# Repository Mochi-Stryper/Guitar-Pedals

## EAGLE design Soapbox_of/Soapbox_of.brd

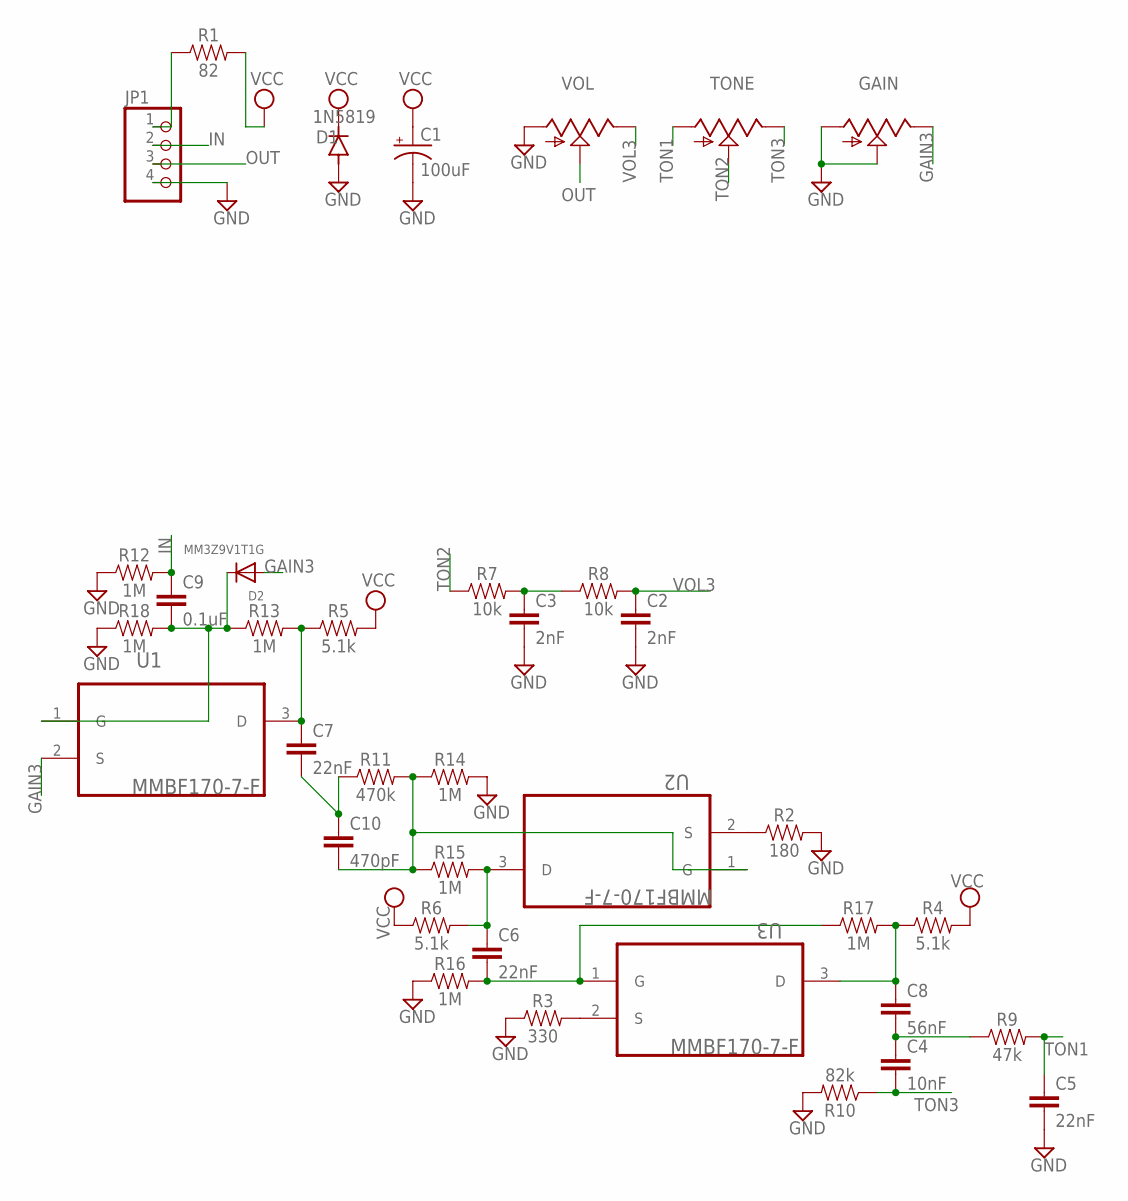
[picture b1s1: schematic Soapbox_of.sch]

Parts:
C1: 100uF; PAN_B_SMD+THRU
C2, C3: 2nF; 0603
C4: 10nF; 0603
C5, C6, C7: 22nF; 0603
C8: 56nF; 0603
C9: 0.1uF; 0603
C10: 470pF; 0603
D1: 1N5819; SOD123
D2: MM3Z9V1T1G; SOD-323F
GAIN: 9MM_SNAP-IN_POT_; 9MM_SNAP-IN_POT
JP1: PINHD-1X4; 1X04
R1: 82; 0603
R2: 180; 0603
R3: 330; 0603
R4, R5, R6: 5.1k; 0603
R7, R8: 10k; 0603
R9: 47k; 0603
R10: 82k; 0603
R11: 470k; 0603
R12, R13, R14, R15, R16, R17, R18: 1M; 0603
TONE: 9MM_SNAP-IN_POT_; 9MM_SNAP-IN_POT
U1, U2, U3: MMBF170-7-F; SOT103P240X110-3N
VOL: 9MM_SNAP-IN_POT_; 9MM_SNAP-IN_POT

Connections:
GAIN3: D2.A, GAIN.3 (E), U1.2 (S)
GND: C1.-, C1.-- (-), C2.2, C3.2, C5.2, D1.A, GAIN.1 (A), GAIN.2 (S), JP1.4, R2.2, R3.1, R10.2, R12.1, R14.2, R16.1, R18.1, VOL.1 (A)
IN: C9.1, JP1.2, R12.2
unnamed: C9.2, D2.C, R13.1, R18.2, U1.1 (G)
unnamed: JP1.1, R1.1
unnamed: R2.1, U2.2 (S)
unnamed: C7.1, R5.1, R13.2, U1.3 (D)
unnamed: C7.2, C10.1, R11.1
unnamed: C10.2, R11.2, R14.1, R15.1, U2.1 (G)
unnamed: C6.1, R6.2, R15.2, U2.3 (D)
unnamed: C6.2, R16.2, R17.1, U3.1 (G)
unnamed: C8.1, R4.1, R17.2, U3.3 (D)
unnamed: C4.1, C8.2, R9.1
unnamed: R3.2, U3.2 (S)
unnamed: C3.1, R7.2, R8.1
OUT: JP1.3, VOL.2 (S)
TON1: C5.1, R9.2, TONE.1 (A)
TON2: R7.1, TONE.2 (S)
TON3: C4.2, R10.1, TONE.3 (E)
VCC: C1.+, C1.++ (+), D1.C, R1.2, R4.2, R5.2, R6.1
VOL3: C2.1, R8.2, VOL.3 (E)

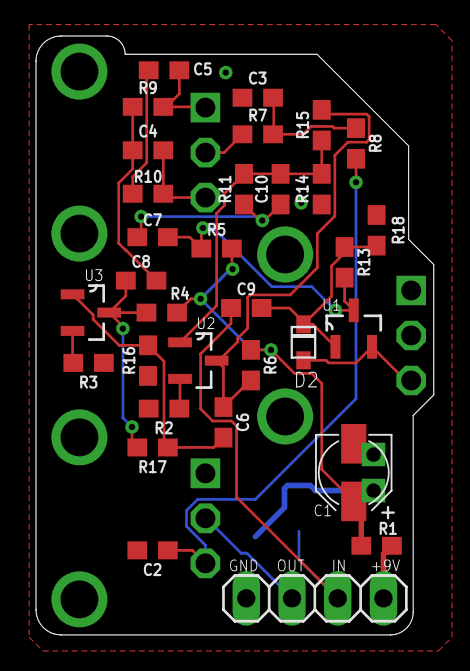
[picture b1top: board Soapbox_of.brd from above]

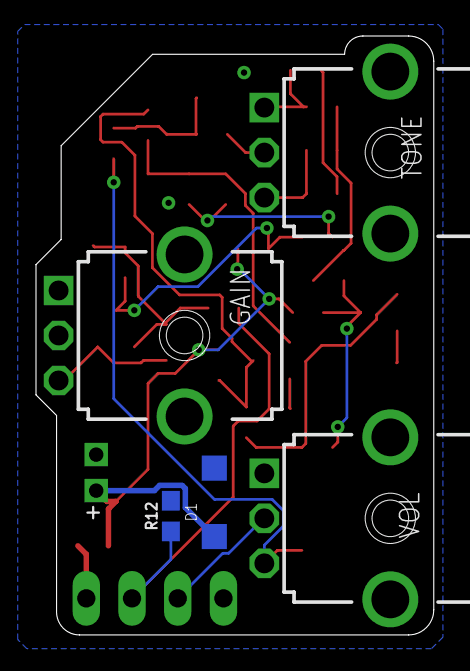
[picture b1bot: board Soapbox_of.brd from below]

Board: 2 copper layers, 22.1 x 33.3 mm, 37 parts (5 on the bottom side), 21 nets.

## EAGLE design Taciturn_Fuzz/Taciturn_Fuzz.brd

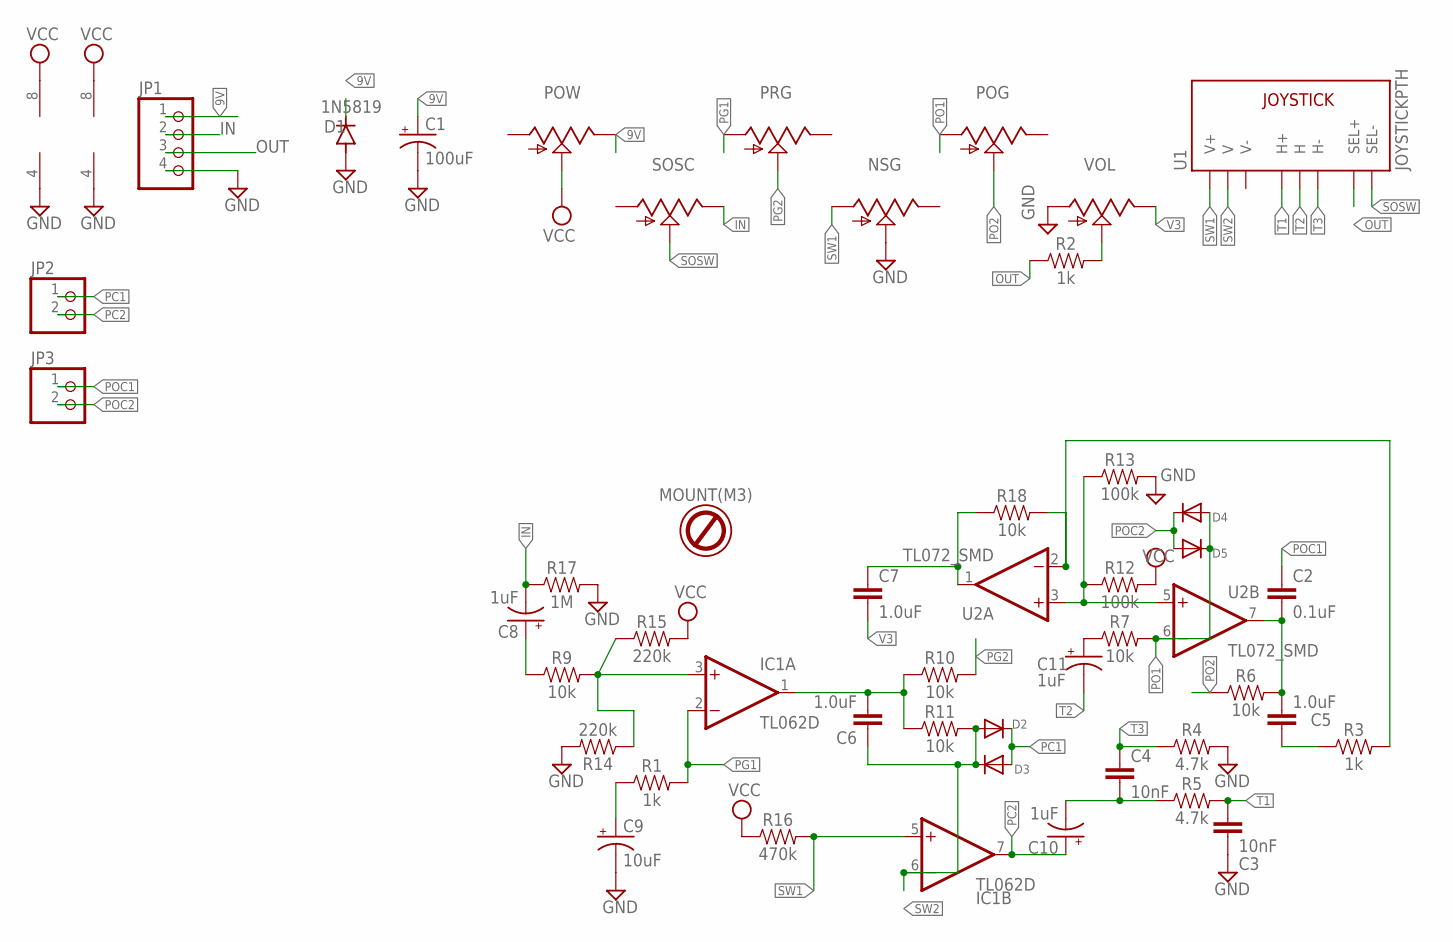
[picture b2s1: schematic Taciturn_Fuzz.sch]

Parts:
C1: 100uF; PAN_B_SMD+THRU
C2: 0.1uF; 0603
C3, C4: 10nF; 0603
C5, C6, C7: 1.0uF; 0603
C8, C10, C11: 1uF; PAN_B_SMD+THRU
C9: 10uF; PAN_B_SMD+THRU
D1: 1N5819; SOD123
D2, D3, D4, D5: DIODESMA; SMADIODE
IC1: TL062D; SO08
JP1: PINHD-1X4; 1X04
JP2, JP3: PINHD-1X2; 1X02
NSG: 9MM_SNAP-IN_POT_; 9MM_SNAP-IN_POT
O1: MOUNT(M3); HOLE-3.5MM
POG: 9MM_SNAP-IN_POT_; 9MM_SNAP-IN_POT
POW: 9MM_SNAP-IN_POT_; 9MM_SNAP-IN_POT
PRG: 9MM_SNAP-IN_POT_; 9MM_SNAP-IN_POT
R1, R2, R3: 1k; 0603
R4, R5: 4.7k; 0603
R6, R7, R9, R10, R11, R18: 10k; 0603
R12, R13: 100k; 0603
R14, R15: 220k; 0603
R16: 470k; 0603
R17: 1M; 0603
SOSC: 9MM_SNAP-IN_POT_; 9MM_SNAP-IN_POT
U1: JOYSTICKPTH; JOYSTICK
U2: TL072_SMD; SO08
VOL: 9MM_SNAP-IN_POT_; 9MM_SNAP-IN_POT

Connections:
9V: C1.+, C1.++ (+), D1.C, JP1.1, POW.3 (E)
GND: C1.-, C1.-- (-), C3.2, C9.-, C9.-- (-), D1.A, IC1.4 (V-), JP1.4, NSG.2 (S), R4.2, R13.2, R14.2, R17.2, U2.4 (V-), VOL.1 (A)
IN: C8.-, C8.-- (-), JP1.2, R17.1, SOSC.3 (E)
unnamed: R3.2, R18.2, U2.2 (-IN)
unnamed: C8.+, C8.++ (+), R9.1
unnamed: IC1.3 (+IN), R9.2, R14.1, R15.1
unnamed: C9.+, C9.++ (+), R1.1
unnamed: C6.2, IC1.1 (OUT), R10.1, R11.1
unnamed: C4.2, C10.-, C10.-- (-), R5.1
unnamed: C11.+, C11.++ (+), R7.1
unnamed: C2.2, C5.1, R6.2, U2.7 (OUT)
unnamed: C5.2, R3.1
unnamed: R12.1, R13.1, U2.3 (+IN), U2.5 (+IN)
unnamed: C7.1, R18.1, U2.1 (OUT)
OUT: JP1.3, R2.1, U1.B1A (SEL+)
PC1: D2.C, D3.A, JP2.1
PC2: C10.+, C10.++ (+), IC1.7 (OUT), JP2.2
PG1: IC1.2 (-IN), PRG.1 (A), R1.2
PG2: PRG.2 (S), R10.2
PO1: D4.A, D5.C, POG.1 (A), R7.2, U2.6 (-IN)
PO2: POG.2 (S), R6.1
POC1: C2.1, JP3.1
POC2: D4.C, D5.A, JP3.2
SOSW: SOSC.2 (S), U1.B2A (SEL-)
SW1: IC1.5 (+IN), NSG.1 (A), R16.2, U1.V1 (V+)
SW2: C6.1, D2.A, D3.C, IC1.6 (-IN), R11.2, U1.V2 (V)
T1: C3.1, R5.2, U1.H1 (H+)
T2: C11.-, C11.-- (-), U1.H2 (H)
T3: C4.1, R4.1, U1.H3 (H-)
V2: R2.2, VOL.2 (S)
V3: C7.2, VOL.3 (E)
VCC: IC1.8 (V+), POW.2 (S), R12.2, R15.2, R16.1, U2.8 (V+)

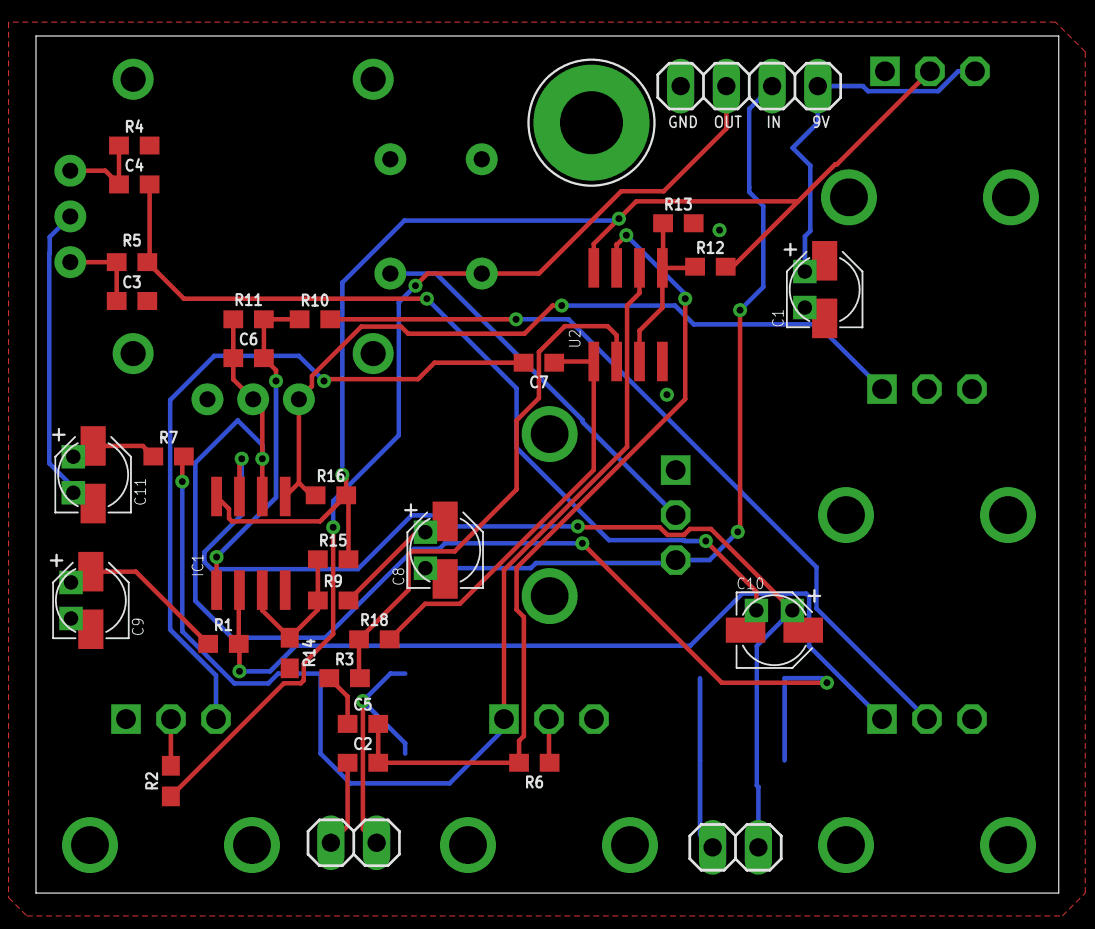
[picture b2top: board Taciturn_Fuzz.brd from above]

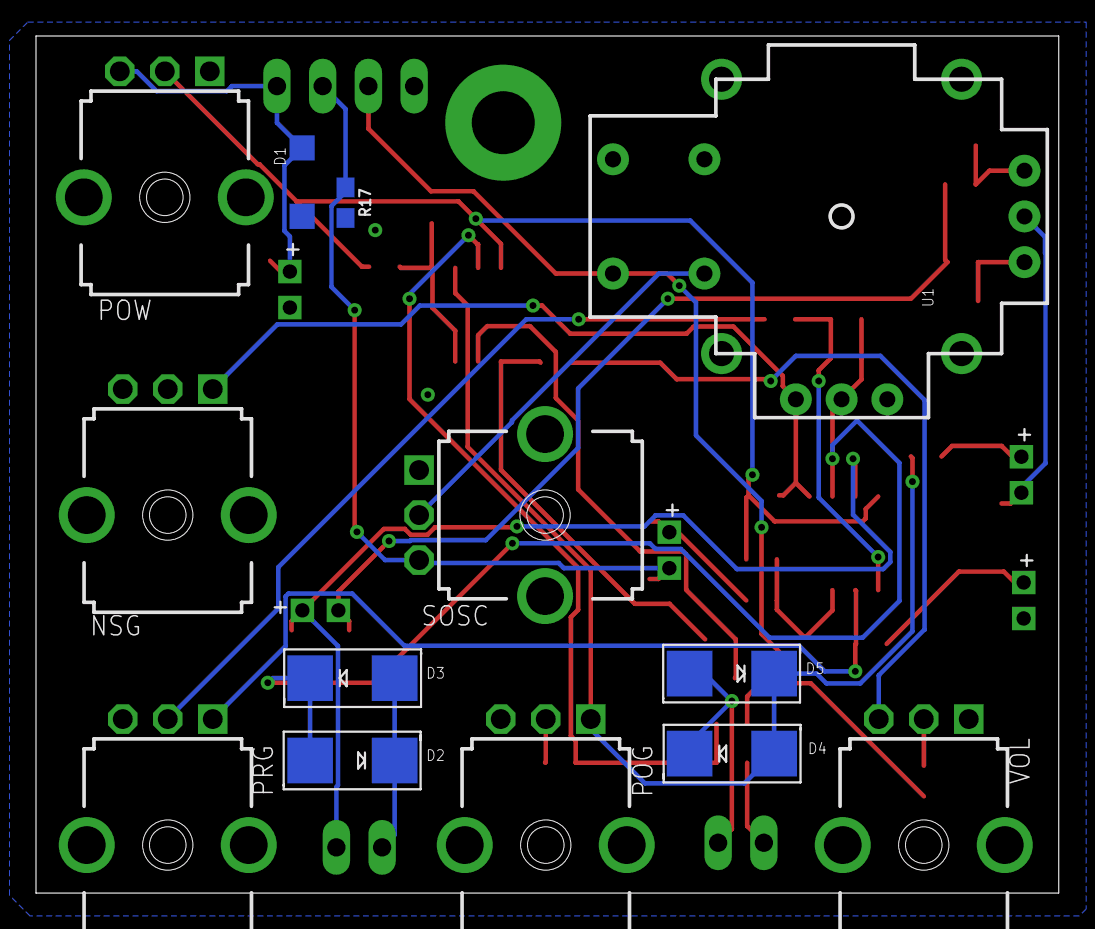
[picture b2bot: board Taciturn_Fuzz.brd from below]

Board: 2 copper layers, 56.8 x 47.6 mm, 46 parts (13 on the bottom side), 32 nets.

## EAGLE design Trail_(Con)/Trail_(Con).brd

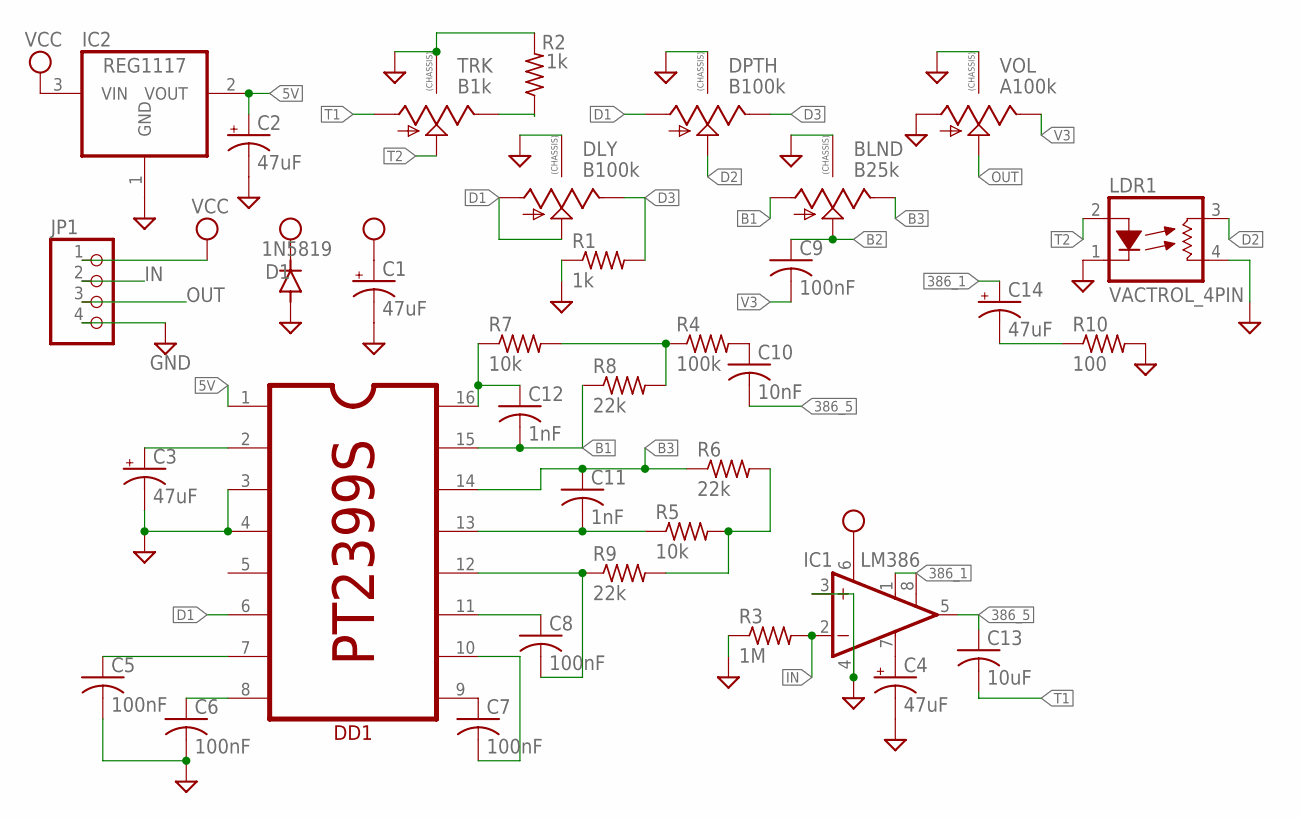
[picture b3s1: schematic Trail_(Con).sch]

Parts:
BLND: B25k; 9MM_SNAP-IN_POT
C1, C2, C3, C4, C14: 47uF; PAN_B_SMD+THRU
C5, C6, C7, C8, C9: 100nF; C0402
C10: 10nF; C0402
C11, C12: 1nF; C0402
C13: 10uF; C0805
D1: 1N5819; SOD123
DD1: PT2399S; SO-16
DLY: B100k; 9MM_SNAP-IN_POT
DPTH: B100k; 9MM_SNAP-IN_POT
IC1: LM386; SO08
IC2: REG1117; SOT223
JP1: PINHD-1X4; 1X04
LDR1: VACTROL_4PIN; VACTROL_4PIN_VTL5C
R1, R2: 1k; R0402
R3: 1M; R0402
R4: 100k; R0402
R5, R7: 10k; R0402
R6, R8, R9: 22k; R0402
R10: 100; R0402
TRK: B1k; 9MM_SNAP-IN_POT
VOL: A100k; 9MM_SNAP-IN_POT

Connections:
5V: C2.+, C2.++ (+), DD1.1, IC2.2 (VOUT)
386_1: C14.+, C14.++ (+), IC1.1 (GAIN), IC1.8 (GAIN)
386_5: C10.2, C13.1, IC1.5 (OUT)
B1: BLND.1 (A), C12.2, DD1.15, R8.1
B2: BLND.2 (S), C9.1
B3: BLND.3 (E), C11.1, DD1.14, R6.1
D1: DD1.6, DLY.1 (A), DLY.2 (S), DPTH.1 (A)
D2: DPTH.2 (S), LDR1.3 (RES1)
D3: DLY.3 (E), DPTH.3 (E), R1.2
GND: BLND.CHASSIS1, BLND.CHASSIS2, C1.-, C1.-- (-), C2.-, C2.-- (-), C3.-, C3.-- (-), C4.-, C4.-- (-), C5.2, C6.2, D1.A, DD1.3, DD1.4, DLY.CHASSIS1, DLY.CHASSIS2, DPTH.CHASSIS1, DPTH.CHASSIS2, IC1.3 (+IN), IC1.4 (GND), IC2.1 (GND), JP1.4, LDR1.1 (LED-), LDR1.4 (RES2), R1.1, R2.2, R3.1, R10.2, TRK.CHASSIS1, TRK.CHASSIS2, VOL.1 (A), VOL.CHASSIS1, VOL.CHASSIS2
IN: IC1.2 (-IN), JP1.2, R3.2
unnamed: C3.+, C3.++ (+), DD1.2
unnamed: C5.1, DD1.7
unnamed: C6.1, DD1.8
unnamed: C7.1, DD1.9
unnamed: C7.2, DD1.10
unnamed: C8.1, DD1.11
unnamed: C8.2, DD1.12, R9.1
unnamed: C11.2, DD1.13, R5.1
unnamed: R5.2, R6.2, R9.2
unnamed: C12.1, DD1.16, R7.1
unnamed: R4.1, R7.2, R8.2
unnamed: C10.1, R4.2
unnamed: R2.1, TRK.3 (E)
unnamed: C4.+, C4.++ (+), IC1.7 (BYPASS)
unnamed: C14.-, C14.-- (-), R10.1
OUT: JP1.3, VOL.2 (S)
T1: C13.2, TRK.1 (A)
T2: LDR1.2 (LED+), TRK.2 (S)
V3: C9.2, VOL.3 (E)
VCC: C1.+, C1.++ (+), D1.C, IC1.6 (VS), IC2.3 (VIN), JP1.1

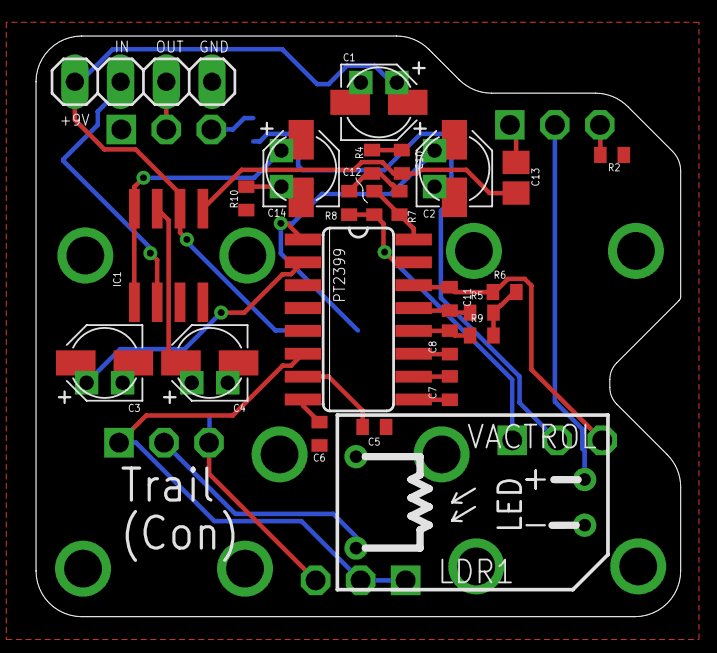
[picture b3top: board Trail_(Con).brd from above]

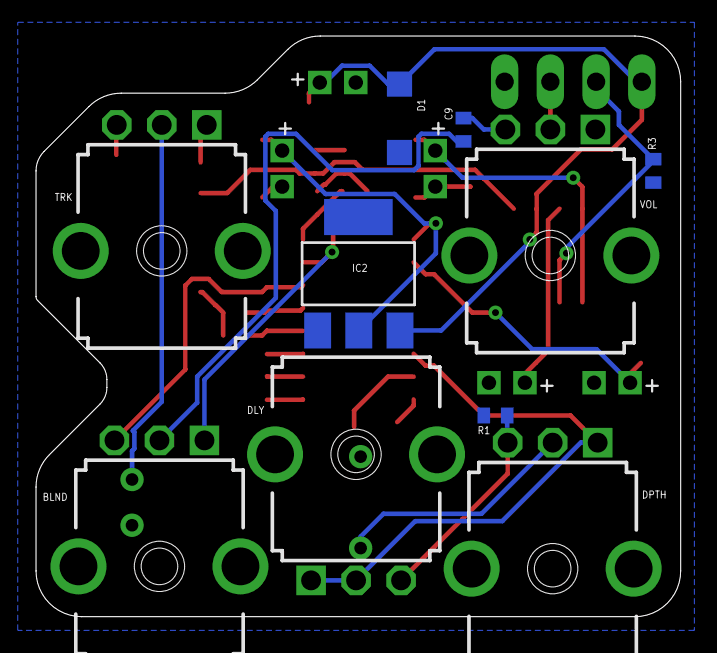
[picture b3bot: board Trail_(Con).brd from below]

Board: 2 copper layers, 35.8 x 32.3 mm, 35 parts (10 on the bottom side), 31 nets.

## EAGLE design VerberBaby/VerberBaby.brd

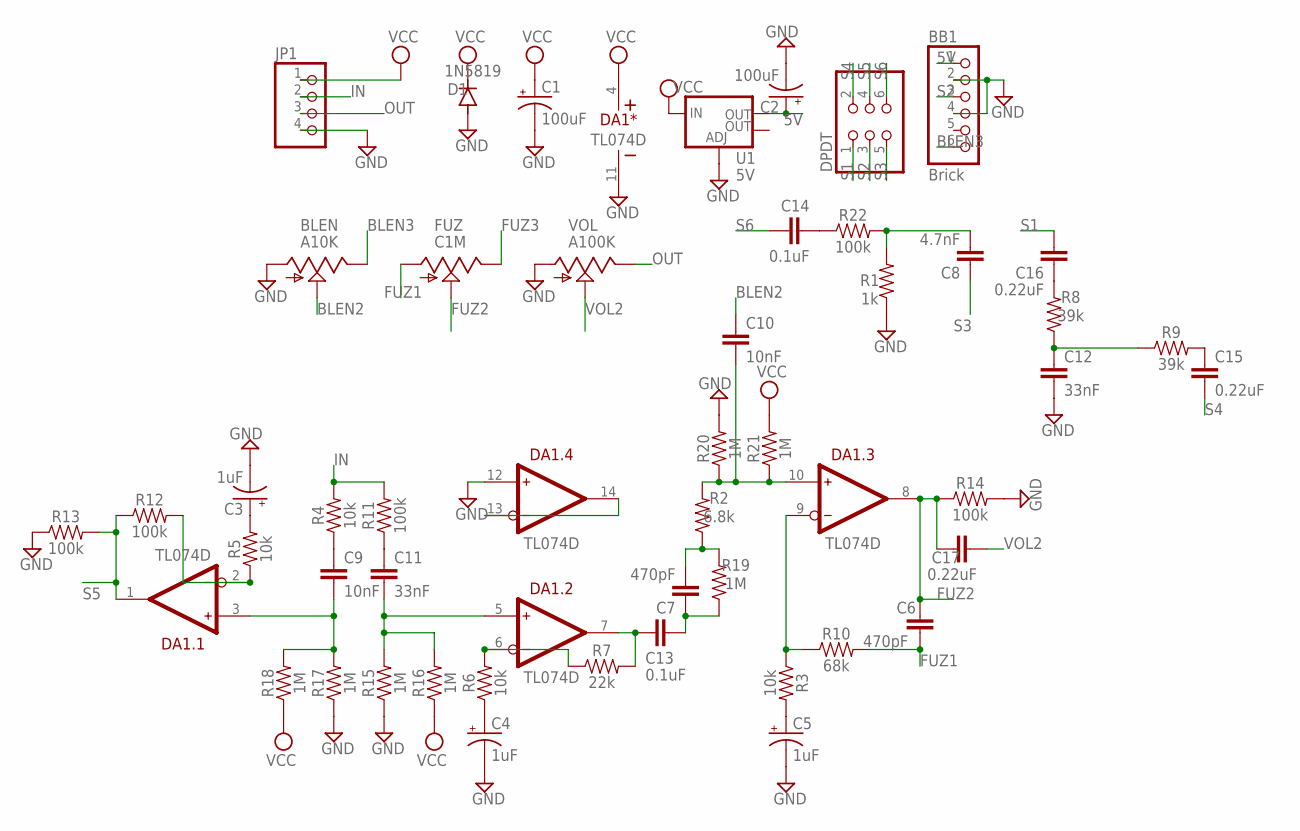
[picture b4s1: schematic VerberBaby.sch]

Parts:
BB1: Brick; 1X06
BLEN: A10K; 9MM_SNAP-IN_POT
C1, C2: 100uF; PAN_B_SMD+THRU
C3, C4, C5: 1uF; PAN_B_SMD+THRU
C6, C7: 470pF; 0603
C8: 4.7nF; 0603
C9, C10: 10nF; 0603
C11, C12: 33nF; 0603
C13, C14: 0.1uF; 0603
C15, C16, C17: 0.22uF; 0603
D1: 1N5819; SOD123
DA1: TL074D; SO-14
DPDT: PINHD-2X3; 2X03
FUZ: C1M; 9MM_SNAP-IN_POT
JP1: PINHD-1X4; 1X04
R1: 1k; 0603
R2: 6.8k; 0603
R3, R4, R5, R6: 10k; 0603
R7: 22k; 0603
R8, R9: 39k; 0603
R10: 68k; 0603
R11, R12, R13, R14, R22: 100k; 0603
R15, R16, R17, R18, R19, R20, R21: 1M; 0603
U1: 5V; SOT223
VOL: A100K; 9MM_SNAP-IN_POT

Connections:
5V: BB1.1, C2.+, C2.++ (+), U1.2 (OUT)
BLEN2: BLEN.2 (S), C10.1
BLEN3: BB1.6, BLEN.3 (E)
FUZ1: C6.2, FUZ.1 (A), R10.2
FUZ2: C6.1, C17.1, DA1.8 (OUT), FUZ.2 (S), R14.1
FUZ3: FUZ.3 (E)
GND: BB1.2, BB1.4, BLEN.1 (A), C1.-, C1.-- (-), C2.-, C2.-- (-), C3.-, C3.-- (-), C4.-, C4.-- (-), C5.-, C5.-- (-), C12.2, D1.A, DA1.11 (V-), DA1.12 (IN+), JP1.4, R1.1, R13.1, R14.2, R15.1, R17.1, R20.2, U1.1 (ADJ), VOL.1 (A)
IN: JP1.2, R4.2, R11.2
N1: DA1.9 (IN-), R3.1, R10.1
unnamed: C11.1, R11.1
unnamed: C9.1, R4.1
unnamed: C11.2, DA1.5 (IN+), R15.2, R16.2
unnamed: C9.2, DA1.3 (IN+), R17.2, R18.2
unnamed: DA1.2 (IN-), R5.1, R12.2
unnamed: C3.+, C3.++ (+), R5.2
unnamed: DA1.6 (IN-), R6.2, R7.1
unnamed: C4.+, C4.++ (+), R6.1
unnamed: C13.2, DA1.7 (OUT), R7.2
unnamed: C7.1, C13.1, R19.1
unnamed: C7.2, R2.1, R19.2
unnamed: C10.2, DA1.10 (IN+), R2.2, R20.1, R21.1
unnamed: DA1.13 (IN-), DA1.14 (OUT)
unnamed: C5.+, C5.++ (+), R3.2
unnamed: C14.2, R22.1
unnamed: C8.2, R1.2, R22.2
unnamed: C16.1, R8.2
unnamed: C12.1, R8.1, R9.1
unnamed: C15.1, R9.2
OUT: JP1.3, VOL.3 (E)
S1: C16.2, DPDT.1
S2: BB1.3, DPDT.3
S3: C8.1, DPDT.5
S4: C15.2, DPDT.2
S5: DA1.1 (OUT), DPDT.4, R12.1, R13.2
S6: C14.1, DPDT.6
VCC: C1.+, C1.++ (+), D1.C, DA1.4 (V+), JP1.1, R16.1, R18.1, R21.2, U1.3 (IN)
VOL2: C17.2, VOL.2 (S)

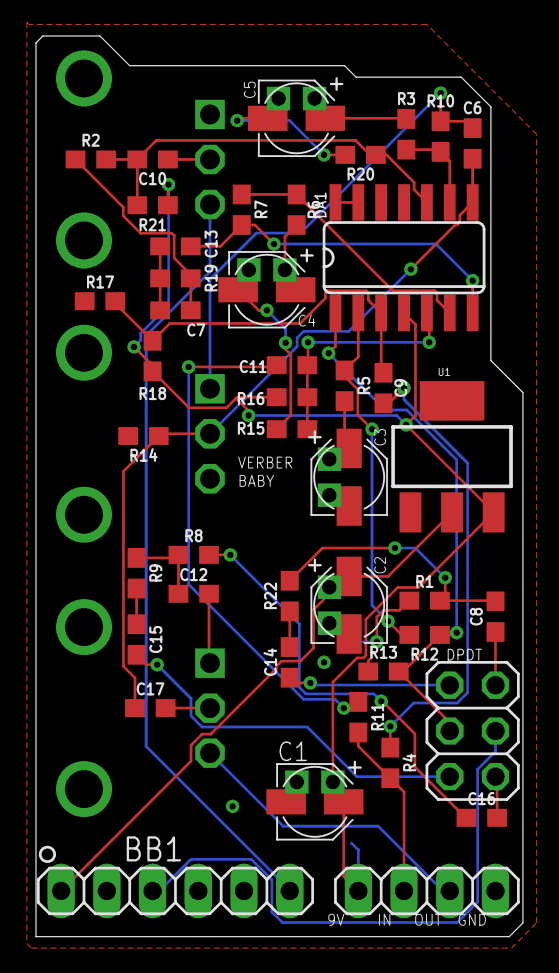
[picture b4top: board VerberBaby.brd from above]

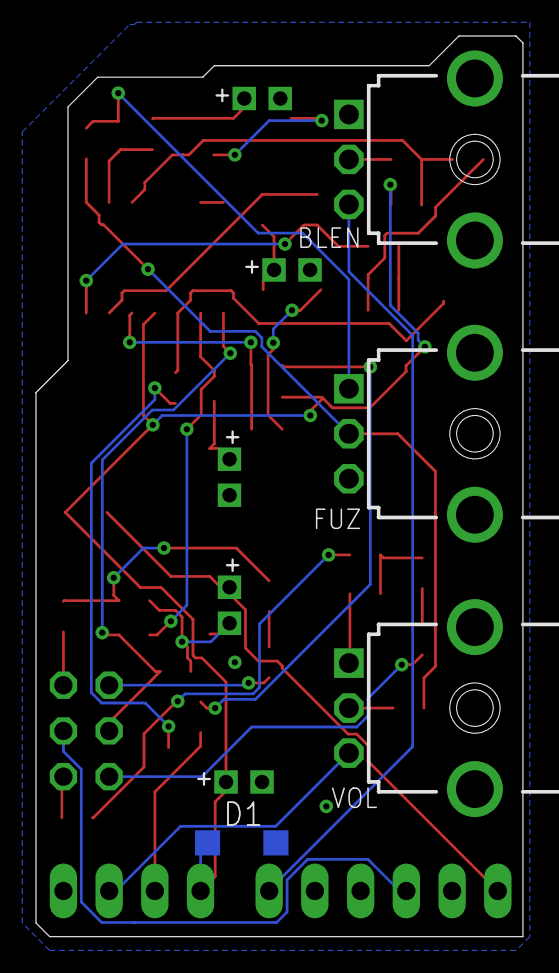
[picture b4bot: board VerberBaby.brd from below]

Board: 2 copper layers, 27.1 x 50.0 mm, 48 parts (4 on the bottom side), 36 nets.

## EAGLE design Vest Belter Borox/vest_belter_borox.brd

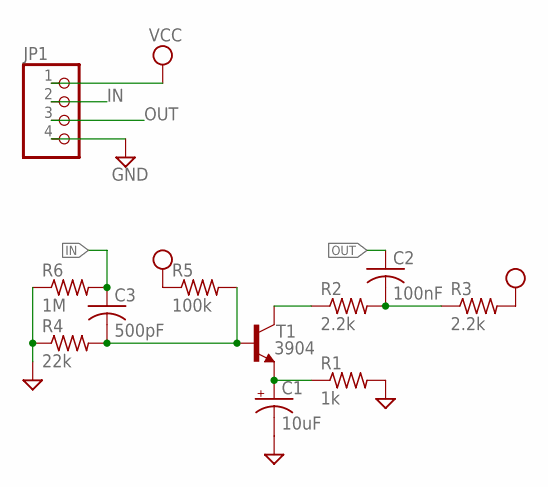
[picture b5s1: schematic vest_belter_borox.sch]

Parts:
C1: 10uF; CAPMP3216X180N
C2: 100nF; C0603
C3: 500pF; C0603
JP1: PINHD-1X4; 1X04
R1: 1k; R0603
R2, R3: 2.2k; R0603
R4: 22k; R0603
R5: 100k; R0603
R6: 1M; R0603
T1: 3904; SOT23-BEC

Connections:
GND: C1.2 (-), JP1.4, R1.2, R4.1, R6.1
IN: C3.1, JP1.2, R6.2
unnamed: C3.2, R4.2, R5.2, T1.B
unnamed: C1.1 (+), R1.1, T1.E
unnamed: C2.2, R2.2, R3.1
unnamed: R2.1, T1.C
OUT: C2.1, JP1.3
VCC: JP1.1, R3.2, R5.1

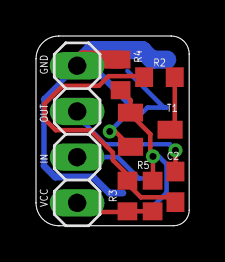
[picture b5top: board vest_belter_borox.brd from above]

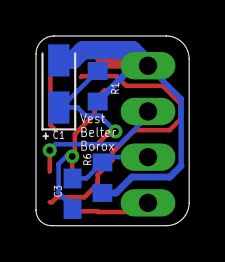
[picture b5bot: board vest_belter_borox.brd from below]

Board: 2 copper layers, 8.5 x 10.5 mm, 11 parts (4 on the bottom side), 8 nets.

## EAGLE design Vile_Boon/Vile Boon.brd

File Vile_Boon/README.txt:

Nocentelli on FSB
Magnalous LuneVibe
Tremolo/Vibrato

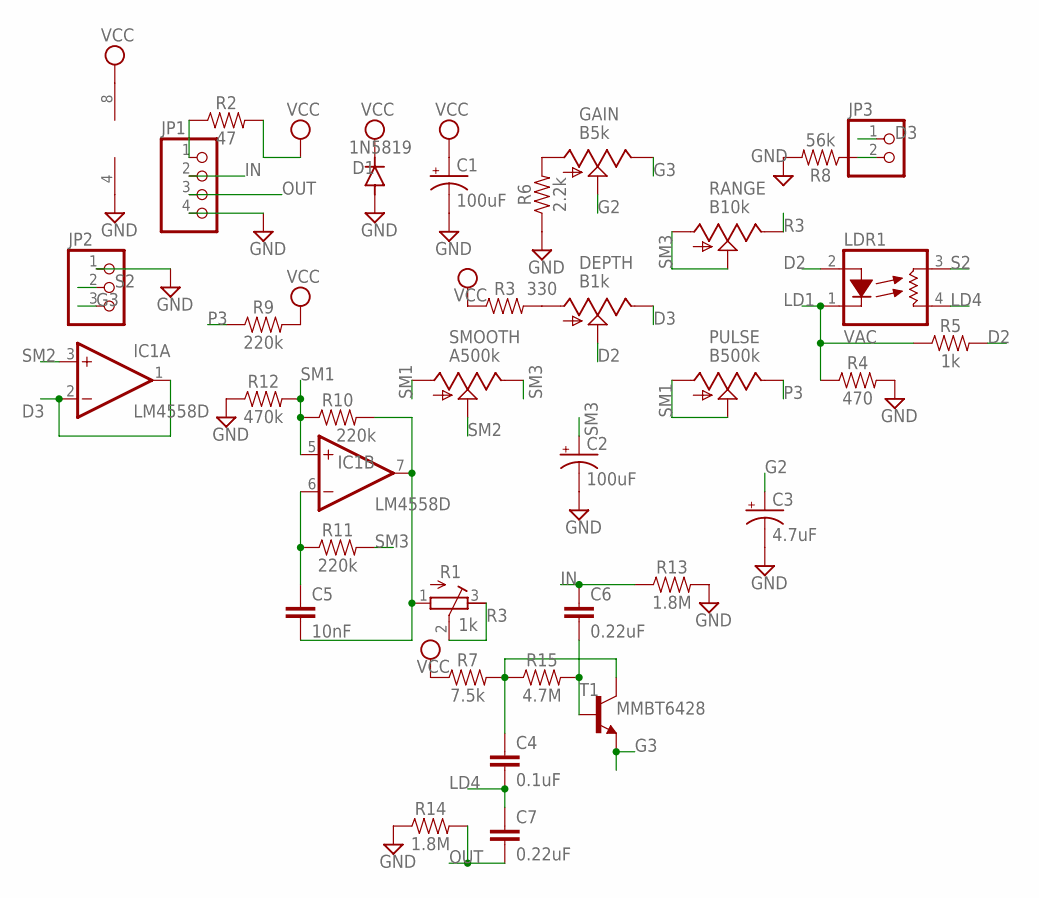
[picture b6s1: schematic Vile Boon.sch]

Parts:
C1, C2: 100uF; PAN_B_SMD+THRU
C3: 4.7uF; PAN_B_SMD+THRU
C4: 0.1uF; 0603
C5: 10nF; 0603
C6, C7: 0.22uF; 0603
D1: 1N5819; SOD123
DEPTH: B1k; 9MM_SNAP-IN_POT
GAIN: B5k; 9MM_SNAP-IN_POT
IC1: LM4558D; SO08
JP1: PINHD-1X4; 1X04
JP2: PINHD-1X3; 1X03
JP3: PINHD-1X2; 1X02
LDR1: VAC; VACTROL_4PIN_VTL5C
PULSE: B500k; 9MM_SNAP-IN_POT
R1: 1k; RTRIM3296W
R2: 47; 0603
R3: 330; 0603
R4: 470; 0603
R5: 1k; 0603
R6: 2.2k; 0603
R7: 7.5k; 0603
R8: 56k; 0603
R9, R10, R11: 220k; 0603
R12: 470k; 0603
R13, R14: 1.8M; 0603
R15: 4.7M; 0603
RANGE: B10k; 9MM_SNAP-IN_POT
SMOOTH: A500k; 9MM_SNAP-IN_POT
T1: MMBT6428; SOT23-BEC

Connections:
D2: DEPTH.2 (S), LDR1.2 (LED+), R5.2
D3: DEPTH.3 (E), IC1.1 (OUT), IC1.2 (-IN), JP3.1
G2: C3.+, C3.++ (+), GAIN.2 (S)
G3: GAIN.3 (E), JP2.3, T1.E
GND: C1.-, C1.-- (-), C2.-, C2.-- (-), C3.-, C3.-- (-), D1.A, IC1.4 (V-), JP1.4, JP2.1, R4.2, R6.1, R8.2, R12.1, R13.2, R14.1
IN: C6.1, JP1.2, R13.1
LD1: LDR1.1 (LED-), R4.1, R5.1
LD4: C4.2, C7.1, LDR1.4 (RES2)
unnamed: C6.2, R15.2, T1.B
unnamed: JP3.2, R8.1
unnamed: C5.1, IC1.6 (-IN), R11.1
unnamed: C5.2, IC1.7 (OUT), R1.1 (A), R10.2
unnamed: DEPTH.1 (A), R3.2
unnamed: C4.1, R7.2, R15.1, T1.C
unnamed: GAIN.1 (A), R6.2
unnamed: JP1.1, R2.1
OUT: C7.2, JP1.3, R14.2
P3: PULSE.3 (E), R9.1
R3: R1.2 (S), R1.3 (E), RANGE.3 (E)
S2: JP2.2, LDR1.3 (RES1)
SM1: IC1.5 (+IN), PULSE.1 (A), PULSE.2 (S), R10.1, R12.2, SMOOTH.1 (A)
SM2: IC1.3 (+IN), SMOOTH.2 (S)
SM3: C2.+, C2.++ (+), R11.2, RANGE.1 (A), RANGE.2 (S), SMOOTH.3 (E)
VCC: C1.+, C1.++ (+), D1.C, IC1.8 (V+), R2.2, R3.1, R7.1, R9.2

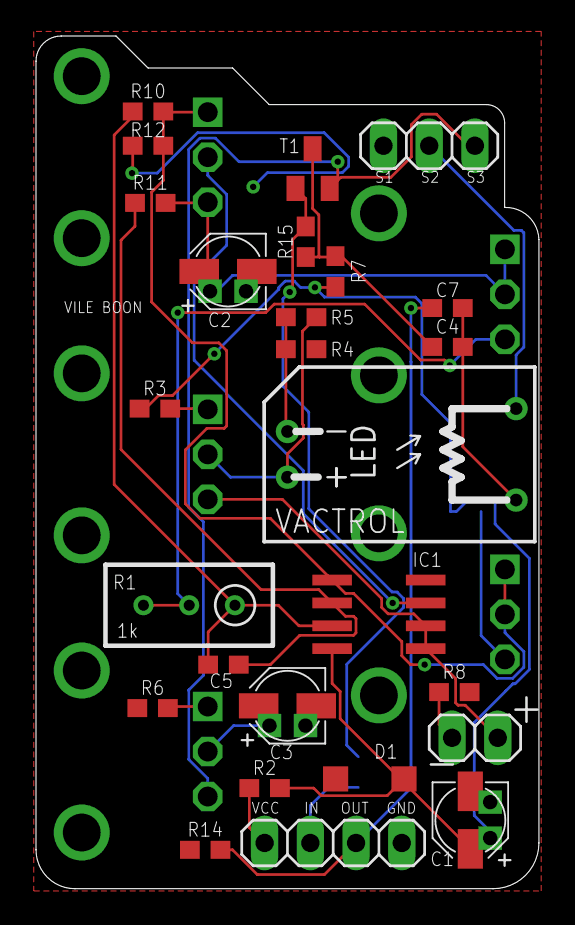
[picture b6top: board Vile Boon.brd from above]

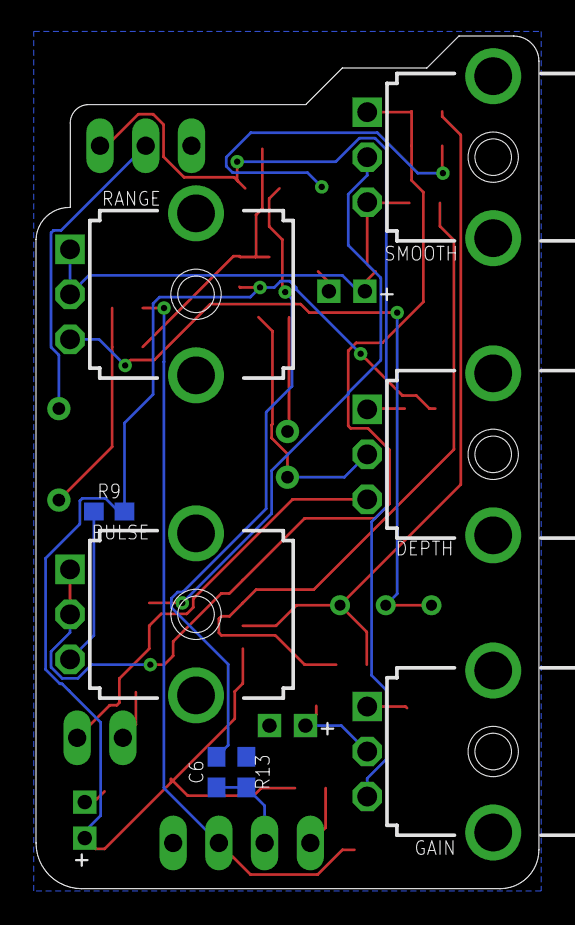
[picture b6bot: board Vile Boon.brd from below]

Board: 2 copper layers, 27.9 x 47.4 mm, 34 parts (8 on the bottom side), 24 nets.

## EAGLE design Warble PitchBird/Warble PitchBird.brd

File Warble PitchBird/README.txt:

Mid-Fi Electronics
Deluxe Pitch Pirate

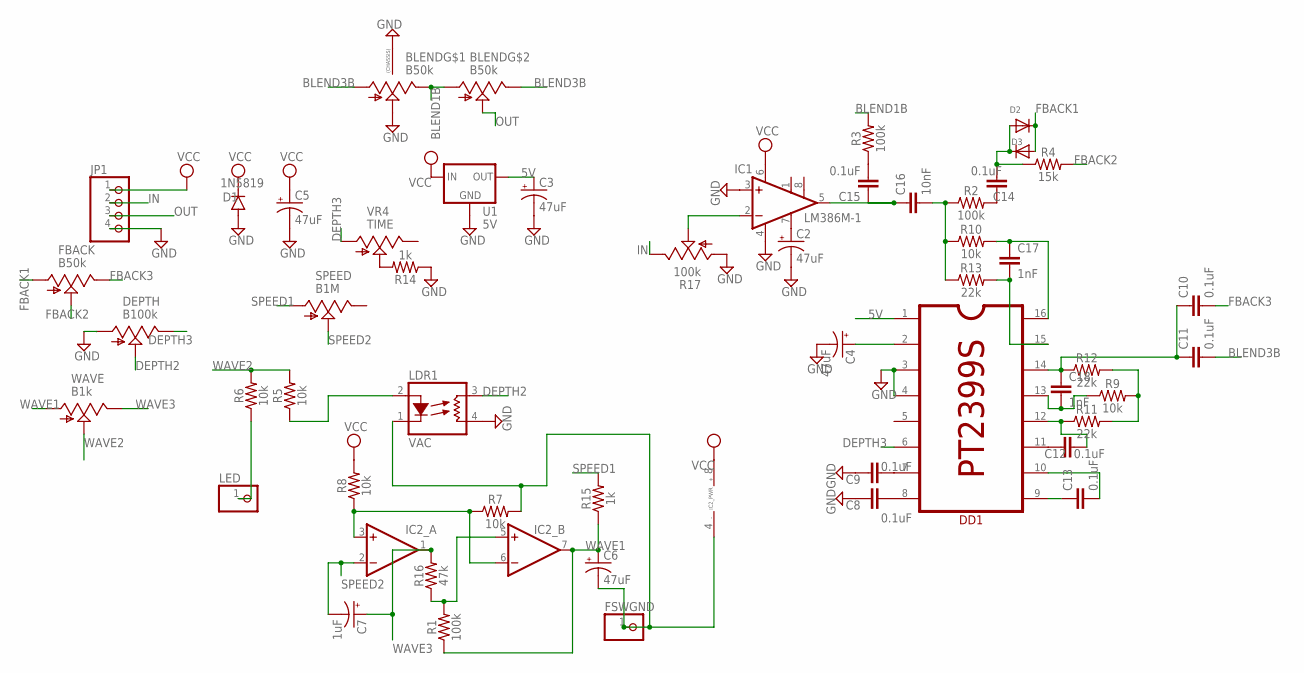
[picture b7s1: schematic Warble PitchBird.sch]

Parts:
BLEND: B50k; DUAL_9MM_SNAP-IN_POT
C2, C3, C4, C5, C6: 47uF; PAN_B_SMD+THRU
C7: 1uF; PAN_B_SMD+THRU
C8, C9, C10, C11, C12, C13, C14, C15: 0.1uF; 0603
C16: 10nF; 0603
C17, C18: 1nF; 0603
D1: 1N5819; SOD123
D2, D3: DIODESOD-123; SOD-123
DD1: PT2399S; SO-16
DEPTH: B100k; 9MM_SNAP-IN_POT
FBACK: B50k; 9MM_SNAP-IN_POT
FSWGND: PINHD-1X1; 1X01
IC1: LM386M-1; SO08
IC2: DUALSMD; SO08
JP1: PINHD-1X4; 1X04
LDR1: VAC; VACTROL_4PIN_VTL5C
LED: PINHD-1X1; 1X01
R1, R2, R3: 100k; 0603
R4: 15k; 0603
R5, R6, R7, R8, R9, R10: 10k; 0603
R11, R12, R13: 22k; 0603
R14, R15: 1k; 0603
R16: 47k; 0603
R17: 100k; PT-10
SPEED: B1M; 9MM_SNAP-IN_POT
U1: 5V; TO-252
VR4: TIME; 9MM_SNAP-IN_POT
WAVE: B1k; 9MM_SNAP-IN_POT

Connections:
5V: C3.+, C3.++ (+), DD1.1, U1.2 (OUT)
BLEND1B: BLEND.1B (A), BLEND.3 (E), R3.2
BLEND3B: BLEND.1 (A), BLEND.3B (E), C11.2
DEPTH2: DEPTH.2 (S), LDR1.3 (RES1)
DEPTH3: DD1.6, DEPTH.3 (E), VR4.1 (A)
FBACK1: D2.C, D3.A, FBACK.1 (A)
FBACK2: FBACK.2 (S), R4.2
FBACK3: C10.2, FBACK.3 (E)
GND: BLEND.2 (S), BLEND.CHASSIS1, BLEND.CHASSIS2, C2.-, C2.-- (-), C3.-, C3.-- (-), C4.-, C4.-- (-), C5.-, C5.-- (-), C8.1, C9.1, D1.A, DD1.3, DD1.4, DEPTH.1 (A), IC1.3 (+IN), IC1.4 (GND), JP1.4, LDR1.4 (RES2), R14.1, R17.A, U1.3 (GND)
IN: JP1.2, R17.E
unnamed: C4.+, C4.++ (+), DD1.2
unnamed: LED.1, R6.1
unnamed: C16.2, R2.1, R10.1, R13.1
unnamed: IC1.2 (-IN), R17.S
unnamed: R14.2, VR4.2 (S)
unnamed: C2.+, C2.++ (+), IC1.7 (BYPASS)
unnamed: C15.1, C16.1, IC1.5 (OUT)
unnamed: C15.2, R3.1
unnamed: C17.1, DD1.16, R10.2
unnamed: C17.2, DD1.15, R13.2
unnamed: C14.1, R2.2
unnamed: C14.2, D2.A, D3.C, R4.1
unnamed: C13.1, DD1.9
unnamed: C13.2, DD1.10
unnamed: C12.1, DD1.11
unnamed: C8.2, DD1.8
unnamed: R9.2, R11.2, R12.2
unnamed: C10.1, C11.1, C18.1, DD1.14, R12.1
unnamed: C18.2, DD1.13, R9.1
unnamed: C12.2, DD1.12, R11.1
unnamed: C9.2, DD1.7
unnamed: IC2.3 (+IN), IC2.6 (-IN), R7.1, R8.1
unnamed: IC2.5 (+IN), R1.2, R16.1
unnamed: LDR1.2 (LED+), R5.1
unnamed: C6.-, C6.-- (-), FSWGND.1, IC2.4 (V-), LDR1.1 (LED-), R7.2
OUT: BLEND.2B (S), JP1.3
SPEED1: R15.2, SPEED.1 (A)
SPEED2: C7.-, C7.-- (-), IC2.2 (-IN), SPEED.2 (S)
VCC: C5.+, C5.++ (+), D1.C, IC1.6 (VS), IC2.8 (V+), JP1.1, R8.2, U1.1 (IN)
WAVE1: C6.+, C6.++ (+), IC2.7 (OUT), R1.1, R15.1, WAVE.1 (A)
WAVE2: R5.2, R6.2, WAVE.2 (S)
WAVE3: C7.+, C7.++ (+), IC2.1 (OUT), R16.2, WAVE.3 (E)

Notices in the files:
parts and their libraries:
SparkFun-Capacitors: Licensing: Creative Commons ShareAlike 4.0 International - https://creativecommons.org/licenses/by-sa/4.0
